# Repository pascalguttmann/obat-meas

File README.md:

# Obat - Measurement

KiCAD Project for the measurement electronics of Obat.

| TOP | BOT |
| ------------- | -------------- |
|  |  |
|  |  |

## License

This repository is licensed under the MIT license.

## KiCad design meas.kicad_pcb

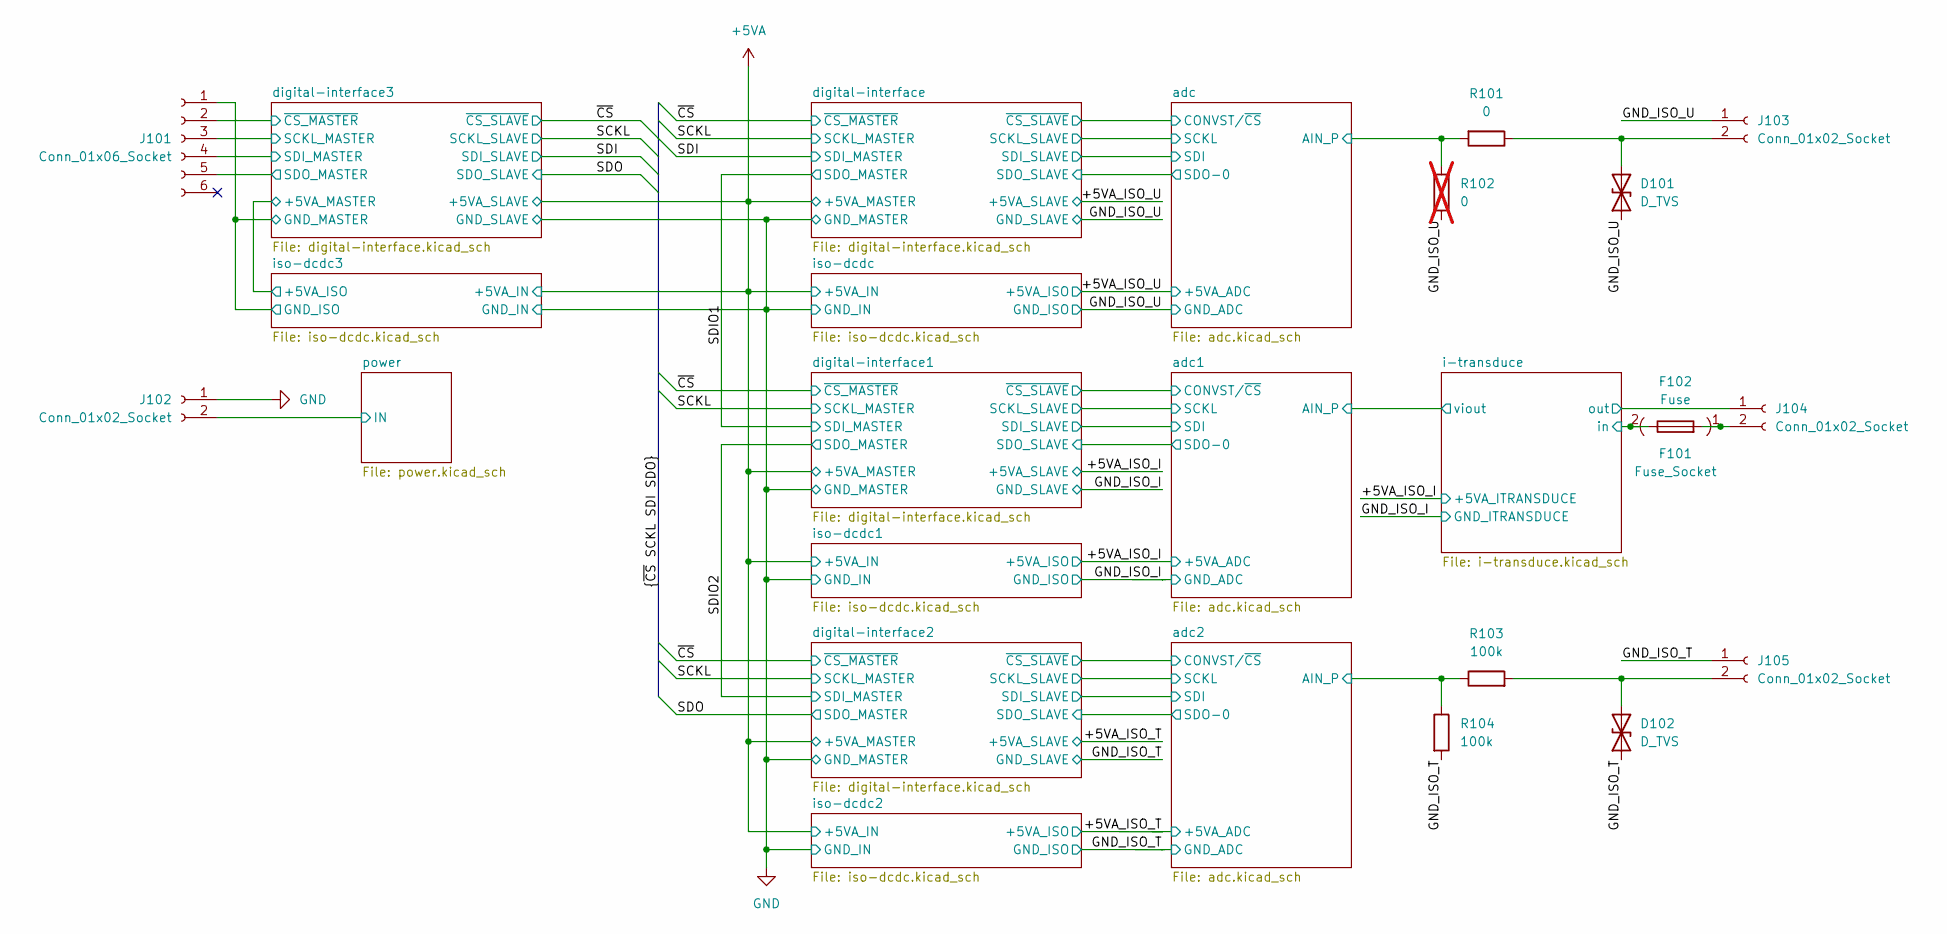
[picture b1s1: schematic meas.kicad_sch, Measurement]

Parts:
D101, D102: D_TVS; D_SOD-323_HandSoldering; MPN UDD32C24L01
F101: Fuse_Socket; FuseHolder_Blade_ATO_Littelfuse_FLR_178.6165; MPN 178.6165.0002
F102: Fuse; MPN 0287030.PXCN
J101: Conn_01x06_Socket; PhoenixContact_TDPT_2,5_6-SP-5,08_1x06_P5.08mm_Horizontal; MPN 1017507
J102, J103, J104, J105: Conn_01x02_Socket; PhoenixContact_TDPT_2,5_2-SP-5,08_1x02_P5.08mm_Horizontal; MPN 1017503
R101: 0; R_1210_3225Metric_Pad1.30x2.65mm_HandSolder; MPN RC1210JR-070RL
R102: 0; R_1210_3225Metric_Pad1.30x2.65mm_HandSolder; MPN RC1210JR-070RL; not fitted
R103, R104: 100k; R_1210_3225Metric_Pad1.30x2.65mm_HandSolder; MPN RC1210FR-07100KL

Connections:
/GND_ISO_T: D102.1 (A1), J105.1, R104.2; also elsewhere on the board
/GND_ISO_U: D101.1 (A1), J103.1, R102.1; also elsewhere on the board
/adc2/AIN_P: R103.1, R104.1; also elsewhere on the board
/adc/AIN_P: R101.2, R102.2; also elsewhere on the board
/digital-interface3/GND_MASTER: J101.1; also elsewhere on the board
/digital-interface3/SCKL_MASTER: J101.3; also elsewhere on the board
/digital-interface3/SDI_MASTER: J101.4; also elsewhere on the board
/digital-interface3/SDO_MASTER: J101.5; also elsewhere on the board
/digital-interface3/~CS_MASTER: J101.2; also elsewhere on the board
/i-transduce/in: F101.2, F102.1; also elsewhere on the board
/i-transduce/out: J104.1; also elsewhere on the board
/power/IN: J102.2; also elsewhere on the board
GND: J102.1; also elsewhere on the board
unnamed: D101.2 (A2), J103.2, R101.1
unnamed: D102.2 (A2), J105.2, R103.2
unnamed: F101.1, F102.2, J104.2

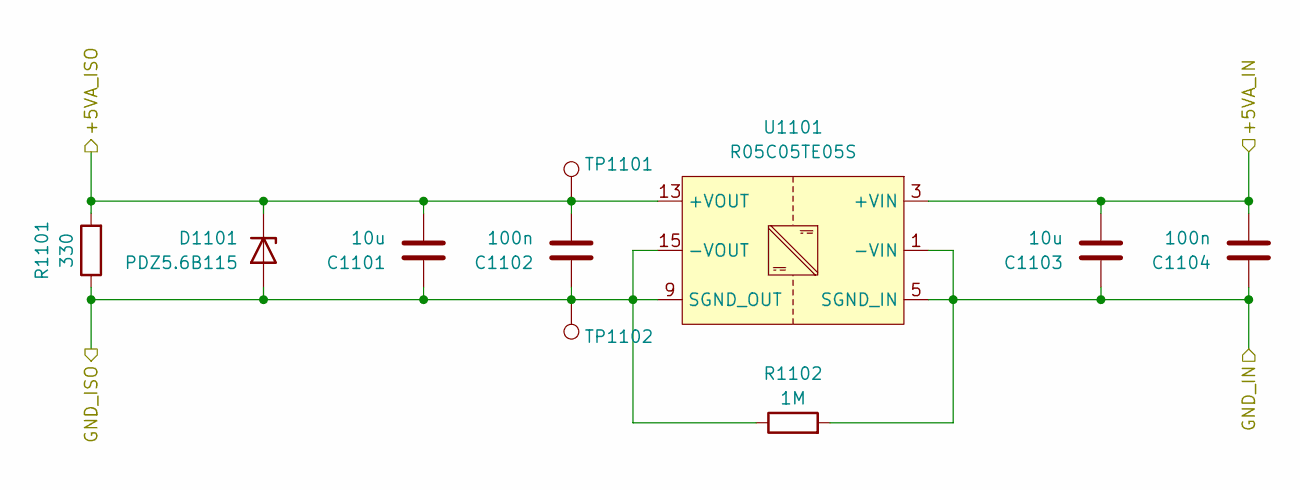
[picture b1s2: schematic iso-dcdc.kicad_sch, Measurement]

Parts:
C1101, C1103: 10u; C_1210_3225Metric_Pad1.33x2.70mm_HandSolder; MPN C1210C106K3RACTU
C1102, C1104: 100n; C_0805_2012Metric_Pad1.18x1.45mm_HandSolder; MPN C0805C104K3RACTU
D1101: PDZ5.6B115; D_SOD-323_HandSoldering; MPN PDZ5.6B,115
R1101: 330; R_1210_3225Metric_Pad1.30x2.65mm_HandSolder; MPN RC1210FR-07330RL
R1102: 1M; R_1210_3225Metric_Pad1.30x2.65mm_HandSolder; MPN RC1210FR-071ML
TP1101, TP1102: TP_0805_2012Metric; MPN RCTCTE
U1101: R05C05TE05S; SOIC-16W_7.5x10.3mm_P1.27mm; MPN R05C05TE05S-R

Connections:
/+5VA_ISO_U: C1101.2, C1102.2, D1101.1 (K), R1101.2, TP1101.1, U1101.13 (+VOUT), U1101.14 (+VOUT); also elsewhere on the board
/GND_ISO_U: C1101.1, C1102.1, D1101.2 (A), R1101.1, R1102.1, TP1102.1, U1101.9 (SGND_OUT), U1101.11 (SGND_OUT), U1101.12 (SGND_OUT), U1101.15 (-VOUT), U1101.16 (-VOUT); also elsewhere on the board
GND: C1103.1, C1104.1, R1102.2, U1101.1 (-VIN), U1101.2 (-VIN), U1101.5 (SGND_IN), U1101.6 (SGND_IN), U1101.7 (SGND_IN), U1101.8 (SGND_IN); also elsewhere on the board

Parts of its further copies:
C1201, C1203, C1301, C1303, C1401, C1403: 10u; C_1210_3225Metric_Pad1.33x2.70mm_HandSolder; MPN C1210C106K3RACTU
C1202, C1204, C1302, C1304, C1402, C1404: 100n; C_0805_2012Metric_Pad1.18x1.45mm_HandSolder; MPN C0805C104K3RACTU
D1201, D1301, D1401: PDZ5.6B115; D_SOD-323_HandSoldering; MPN PDZ5.6B,115
R1201, R1301, R1401: 330; R_1210_3225Metric_Pad1.30x2.65mm_HandSolder; MPN RC1210FR-07330RL
R1202, R1302, R1402: 1M; R_1210_3225Metric_Pad1.30x2.65mm_HandSolder; MPN RC1210FR-071ML
TP1201, TP1202, TP1301, TP1302, TP1401, TP1402: TP_0805_2012Metric; MPN RCTCTE
U1201, U1301, U1401: R05C05TE05S; SOIC-16W_7.5x10.3mm_P1.27mm; MPN R05C05TE05S-R

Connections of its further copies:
/+5VA_ISO_I: C1201.2, C1202.2, D1201.1 (K), R1201.2, TP1201.1, U1201.13 (+VOUT), U1201.14 (+VOUT); also elsewhere on the board
/+5VA_ISO_T: C1301.2, C1302.2, D1301.1 (K), R1301.2, TP1301.1, U1301.13 (+VOUT), U1301.14 (+VOUT); also elsewhere on the board
/GND_ISO_I: C1201.1, C1202.1, D1201.2 (A), R1201.1, R1202.1, TP1202.1, U1201.9 (SGND_OUT), U1201.11 (SGND_OUT), U1201.12 (SGND_OUT), U1201.15 (-VOUT), U1201.16 (-VOUT); also elsewhere on the board
/GND_ISO_T: C1301.1, C1302.1, D1301.2 (A), R1301.1, R1302.1, TP1302.1, U1301.9 (SGND_OUT), U1301.11 (SGND_OUT), U1301.12 (SGND_OUT), U1301.15 (-VOUT), U1301.16 (-VOUT); also elsewhere on the board
/digital-interface3/+5VA_MASTER: C1401.2, C1402.2, D1401.1 (K), R1401.2, TP1401.1, U1401.13 (+VOUT), U1401.14 (+VOUT); also elsewhere on the board
/digital-interface3/GND_MASTER: C1401.1, C1402.1, D1401.2 (A), R1401.1, R1402.1, TP1402.1, U1401.9 (SGND_OUT), U1401.11 (SGND_OUT), U1401.12 (SGND_OUT), U1401.15 (-VOUT), U1401.16 (-VOUT); also elsewhere on the board
GND: C1203.1, C1204.1, C1303.1, C1304.1, C1403.1, C1404.1, R1202.2, R1302.2, R1402.2, U1201.1 (-VIN), U1201.2 (-VIN), U1201.5 (SGND_IN), U1201.6 (SGND_IN), U1201.7 (SGND_IN), U1201.8 (SGND_IN), U1301.1 (-VIN), U1301.2 (-VIN), U1301.5 (SGND_IN), U1301.6 (SGND_IN), U1301.7 (SGND_IN), U1301.8 (SGND_IN), U1401.1 (-VIN), U1401.2 (-VIN), U1401.5 (SGND_IN), U1401.6 (SGND_IN), U1401.7 (SGND_IN), U1401.8 (SGND_IN); also elsewhere on the board

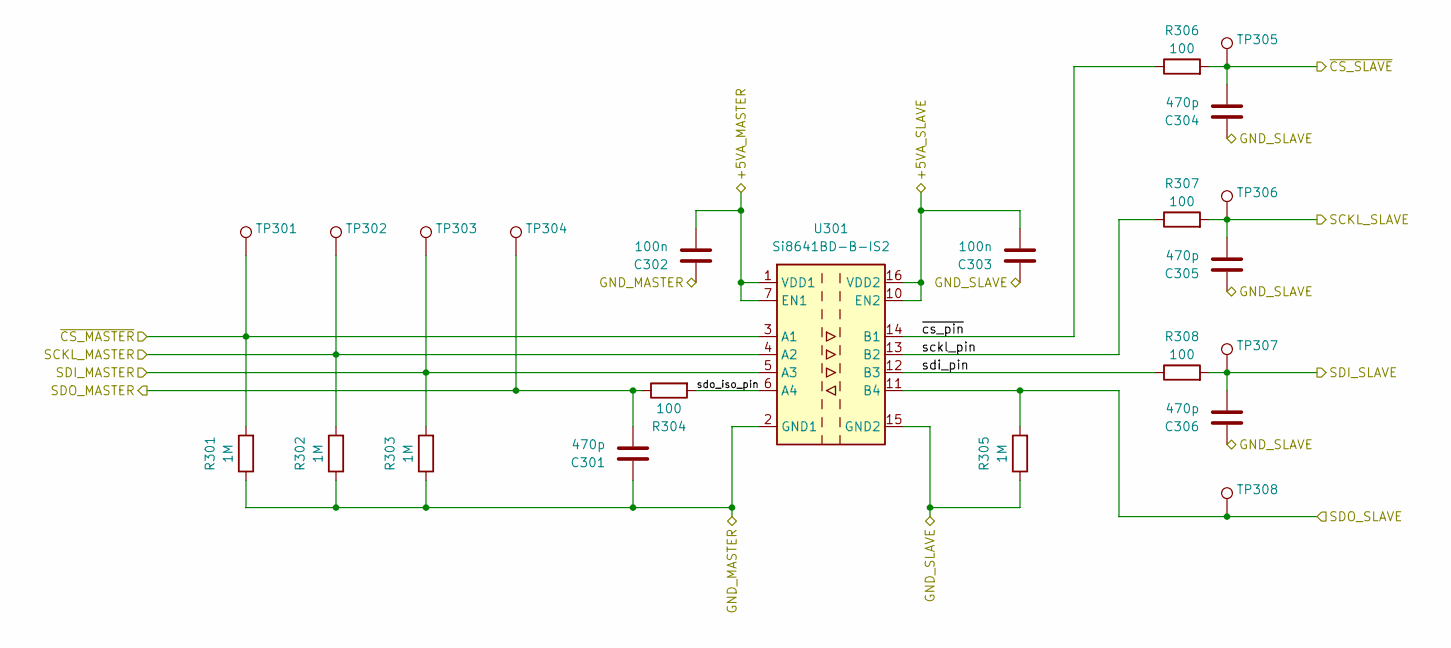
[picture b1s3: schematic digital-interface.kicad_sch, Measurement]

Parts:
C301, C304, C305, C306: 470p; C_0805_2012Metric_Pad1.18x1.45mm_HandSolder; MPN C0805C471K3RACTU
C302, C303: 100n; C_0805_2012Metric_Pad1.18x1.45mm_HandSolder; MPN C0805C104K3RACTU
R301, R302, R303, R305: 1M; R_1210_3225Metric_Pad1.30x2.65mm_HandSolder; MPN RC1210FR-071ML
R304, R306, R307, R308: 100; R_1210_3225Metric_Pad1.30x2.65mm_HandSolder; MPN RC1210FR-07100RL
TP301, TP302, TP303, TP304, TP305, TP306, TP307, TP308: TP_0805_2012Metric; MPN RCTCTE
U301: Si8641BD-B-IS2; SOIC-16W_7.5x10.3mm_P1.27mm; MPN SI8641BD-B-IS2

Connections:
/+5VA_ISO_I: C303.2, U301.10 (EN2), U301.16 (VDD2); also elsewhere on the board
/GND_ISO_I: C303.1, C304.1, C305.1, C306.1, R305.1, U301.9 (GND2), U301.15 (GND2); also elsewhere on the board
/SCKL: R302.2, TP302.1, U301.4 (A2); also elsewhere on the board
/SDIO1: R303.2, TP303.1, U301.5 (A3); also elsewhere on the board
/SDIO2: C301.2, R304.1, TP304.1; also elsewhere on the board
/adc1/CONVST/~CS: C304.2, R306.2, TP305.1; also elsewhere on the board
/adc1/SCKL: C305.2, R307.2, TP306.1; also elsewhere on the board
/adc1/SDI: C306.2, R308.2, TP307.1; also elsewhere on the board
/adc1/SDO-0: R305.2, TP308.1, U301.11 (B4); also elsewhere on the board
/digital-interface1/sckl_pin: R307.1, U301.13 (B2)
/digital-interface1/sdi_pin: R308.1, U301.12 (B3)
/digital-interface1/sdo_iso_pin: R304.2, U301.6 (A4)
/digital-interface1/~cs_pin: R306.1, U301.14 (B1)
/~CS: R301.2, TP301.1, U301.3 (A1); also elsewhere on the board
GND: C301.1, C302.1, R301.1, R302.1, R303.1, U301.2 (GND1), U301.8 (GND1); also elsewhere on the board

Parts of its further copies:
C201, C204, C205, C206, C401, C404, C405, C406, C501, C504, C505, C506: 470p; C_0805_2012Metric_Pad1.18x1.45mm_HandSolder; MPN C0805C471K3RACTU
C202, C203, C402, C403, C502, C503: 100n; C_0805_2012Metric_Pad1.18x1.45mm_HandSolder; MPN C0805C104K3RACTU
R201, R202, R203, R205, R401, R402, R403, R405, R501, R502, R503, R505: 1M; R_1210_3225Metric_Pad1.30x2.65mm_HandSolder; MPN RC1210FR-071ML
R204, R206, R207, R208, R404, R406, R407, R408, R504, R506, R507, R508: 100; R_1210_3225Metric_Pad1.30x2.65mm_HandSolder; MPN RC1210FR-07100RL
TP201, TP202, TP203, TP204, TP205, TP206, TP207, TP208, TP401, TP402, TP403, TP404, TP405, TP406, TP407, TP408, TP501, TP502, TP503, TP504, TP505, TP506, TP507, TP508: TP_0805_2012Metric; MPN RCTCTE
U201, U401, U501: Si8641BD-B-IS2; SOIC-16W_7.5x10.3mm_P1.27mm; MPN SI8641BD-B-IS2

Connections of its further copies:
/+5VA_ISO_T: C403.2, U401.10 (EN2), U401.16 (VDD2); also elsewhere on the board
/+5VA_ISO_U: C203.2, U201.10 (EN2), U201.16 (VDD2); also elsewhere on the board
/GND_ISO_T: C403.1, C404.1, C405.1, C406.1, R405.1, U401.9 (GND2), U401.15 (GND2); also elsewhere on the board
/GND_ISO_U: C203.1, C204.1, C205.1, C206.1, R205.1, U201.9 (GND2), U201.15 (GND2); also elsewhere on the board
/SCKL: C505.2, R202.2, R402.2, R507.2, TP202.1, TP402.1, TP506.1, U201.4 (A2), U401.4 (A2); also elsewhere on the board
/SDI: C506.2, R203.2, R508.2, TP203.1, TP507.1, U201.5 (A3)
/SDIO1: C201.2, R204.1, TP204.1; also elsewhere on the board
/SDIO2: R403.2, TP403.1, U401.5 (A3); also elsewhere on the board
/SDO: C401.2, R404.1, R505.2, TP404.1, TP508.1, U501.11 (B4)
/adc2/CONVST/~CS: C404.2, R406.2, TP405.1; also elsewhere on the board
/adc2/SCKL: C405.2, R407.2, TP406.1; also elsewhere on the board
/adc2/SDI: C406.2, R408.2, TP407.1; also elsewhere on the board
/adc2/SDO-0: R405.2, TP408.1, U401.11 (B4); also elsewhere on the board
/adc/CONVST/~CS: C204.2, R206.2, TP205.1; also elsewhere on the board
/adc/SCKL: C205.2, R207.2, TP206.1; also elsewhere on the board
/adc/SDI: C206.2, R208.2, TP207.1; also elsewhere on the board
/adc/SDO-0: R205.2, TP208.1, U201.11 (B4); also elsewhere on the board
/digital-interface2/sckl_pin: R407.1, U401.13 (B2)
/digital-interface2/sdi_pin: R408.1, U401.12 (B3)
/digital-interface2/sdo_iso_pin: R404.2, U401.6 (A4)
/digital-interface2/~cs_pin: R406.1, U401.14 (B1)
/digital-interface3/+5VA_MASTER: C502.2, U501.1 (VDD1), U501.7 (EN1); also elsewhere on the board
/digital-interface3/GND_MASTER: C501.1, C502.1, R501.1, R502.1, R503.1, U501.2 (GND1), U501.8 (GND1); also elsewhere on the board
/digital-interface3/SCKL_MASTER: R502.2, TP502.1, U501.4 (A2); also elsewhere on the board
/digital-interface3/SDI_MASTER: R503.2, TP503.1, U501.5 (A3); also elsewhere on the board
/digital-interface3/SDO_MASTER: C501.2, R504.1, TP504.1; also elsewhere on the board
/digital-interface3/sckl_pin: R507.1, U501.13 (B2)
/digital-interface3/sdi_pin: R508.1, U501.12 (B3)
/digital-interface3/sdo_iso_pin: R504.2, U501.6 (A4)
/digital-interface3/~CS_MASTER: R501.2, TP501.1, U501.3 (A1); also elsewhere on the board
/digital-interface3/~cs_pin: R506.1, U501.14 (B1)
/digital-interface/sckl_pin: R207.1, U201.13 (B2)
/digital-interface/sdi_pin: R208.1, U201.12 (B3)
/digital-interface/sdo_iso_pin: R204.2, U201.6 (A4)
/digital-interface/~cs_pin: R206.1, U201.14 (B1)
/~CS: C504.2, R201.2, R401.2, R506.2, TP201.1, TP401.1, TP505.1, U201.3 (A1), U401.3 (A1); also elsewhere on the board
GND: C201.1, C202.1, C401.1, C402.1, C503.1, C504.1, C505.1, C506.1, R201.1, R202.1, R203.1, R401.1, R402.1, R403.1, R505.1, U201.2 (GND1), U201.8 (GND1), U401.2 (GND1), U401.8 (GND1), U501.9 (GND2), U501.15 (GND2); also elsewhere on the board

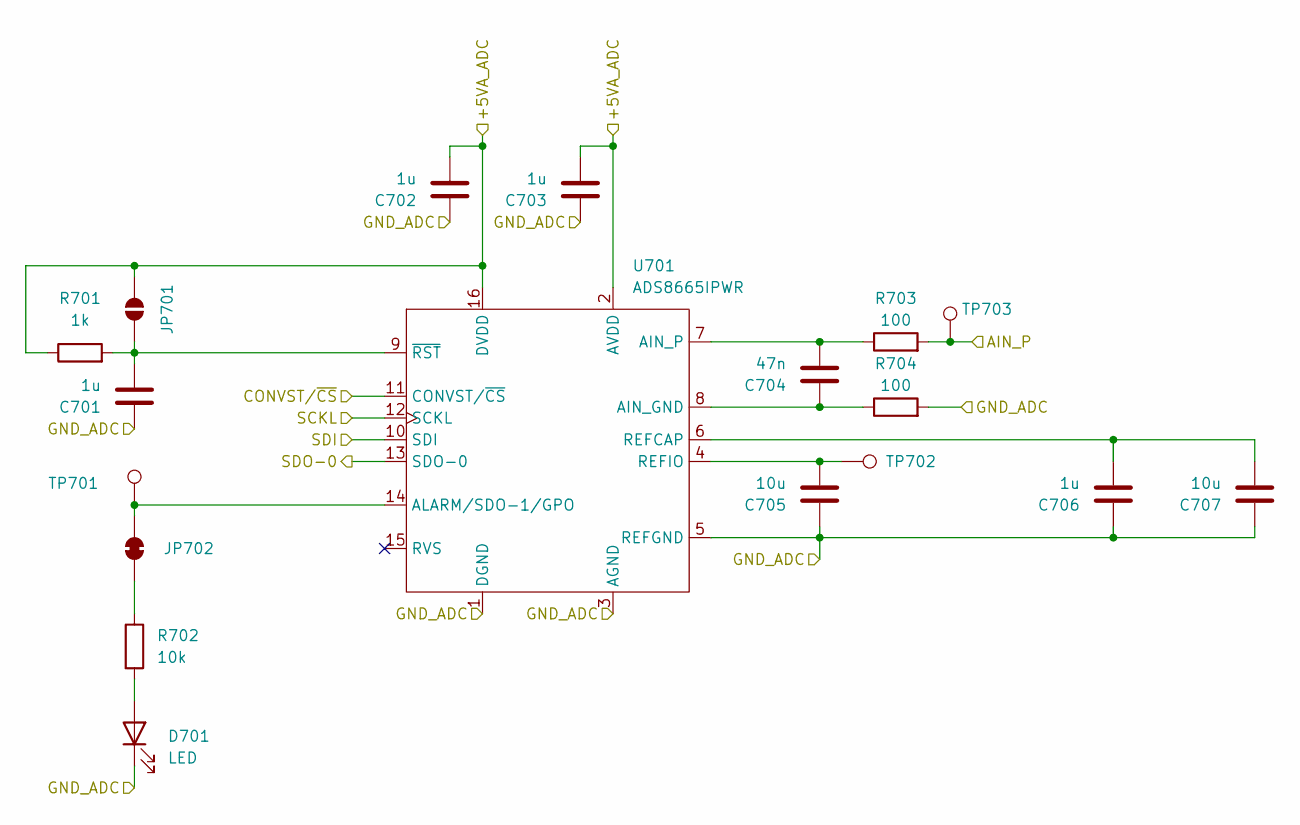
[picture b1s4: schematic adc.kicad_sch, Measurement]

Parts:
C701, C702, C703, C706: 1u; C_0603_1608Metric_Pad1.08x0.95mm_HandSolder; MPN C0603C105K4RACTU
C704: 47n; C_1206_3216Metric_Pad1.33x1.80mm_HandSolder; MPN C1206C473J5GACTU
C705, C707: 10u; C_1210_3225Metric_Pad1.33x2.70mm_HandSolder; MPN C1210C106K3RACTU
D701: LED; LED_0805_2012Metric_Pad1.15x1.40mm_HandSolder; MPN IN-S85CS5G
JP701: SolderJumper_2_Open; SolderJumper-2_P1.3mm_Open_RoundedPad1.0x1.5mm
JP702: SolderJumper_2_Bridged; SolderJumper-2_P1.3mm_Bridged-Soldermask-Paste_RoundedPad1.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
R701: 1k; R_1210_3225Metric_Pad1.30x2.65mm_HandSolder; MPN RC1210FR-071KL
R702: 10k; R_1210_3225Metric_Pad1.30x2.65mm_HandSolder; MPN RC1210FR-0710KL
R703, R704: 100; R_1210_3225Metric_Pad1.30x2.65mm_HandSolder; MPN RC1210FR-07100RL
TP701, TP702, TP703: TP_0805_2012Metric; MPN RCTCTE
U701: ADS8665IPWR; TSSOP-16_4.4x5mm_P0.65mm; MPN ADS8665IPWR

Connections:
/+5VA_ISO_I: C702.2, C703.2, JP701.1 (A), R701.1, U701.2 (AVDD), U701.16 (DVDD); also elsewhere on the board
/GND_ISO_I: C701.1, C702.1, C703.1, C705.1, C706.1, C707.1, D701.1 (K), R704.2, U701.1 (DGND), U701.3 (AGND), U701.5 (REFGND); also elsewhere on the board
/adc1/AIN_P: R703.2, TP703.1; also elsewhere on the board
/adc1/CONVST/~CS: U701.11 (CONVST/~CS); also elsewhere on the board
/adc1/SCKL: U701.12 (SCKL); also elsewhere on the board
/adc1/SDI: U701.10 (SDI); also elsewhere on the board
/adc1/SDO-0: U701.13 (SDO-0); also elsewhere on the board
unnamed: D701.2 (A), R702.2
unnamed: C701.2, JP701.2 (B), R701.2, U701.9 (~RST)
unnamed: JP702.1 (A), R702.1
unnamed: JP702.2 (B), TP701.1, U701.14 (ALARM/SDO-1/GPO)
unnamed: C704.1, R704.1, U701.8 (AIN_GND)
unnamed: C704.2, R703.1, U701.7 (AIN_P)
unnamed: C706.2, C707.2, U701.6 (REFCAP)
unnamed: C705.2, TP702.1, U701.4 (REFIO)

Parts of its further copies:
C601, C602, C603, C606, C801, C802, C803, C806: 1u; C_0603_1608Metric_Pad1.08x0.95mm_HandSolder; MPN C0603C105K4RACTU
C604, C804: 47n; C_1206_3216Metric_Pad1.33x1.80mm_HandSolder; MPN C1206C473J5GACTU
C605, C607, C805, C807: 10u; C_1210_3225Metric_Pad1.33x2.70mm_HandSolder; MPN C1210C106K3RACTU
D601, D801: LED; LED_0805_2012Metric_Pad1.15x1.40mm_HandSolder; MPN IN-S85CS5G
JP601, JP801: SolderJumper_2_Open; SolderJumper-2_P1.3mm_Open_RoundedPad1.0x1.5mm
JP602, JP802: SolderJumper_2_Bridged; SolderJumper-2_P1.3mm_Bridged-Soldermask-Paste_RoundedPad1.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
R601, R801: 1k; R_1210_3225Metric_Pad1.30x2.65mm_HandSolder; MPN RC1210FR-071KL
R602, R802: 10k; R_1210_3225Metric_Pad1.30x2.65mm_HandSolder; MPN RC1210FR-0710KL
R603, R604, R803, R804: 100; R_1210_3225Metric_Pad1.30x2.65mm_HandSolder; MPN RC1210FR-07100RL
TP601, TP602, TP603, TP801, TP802, TP803: TP_0805_2012Metric; MPN RCTCTE
U601, U801: ADS8665IPWR; TSSOP-16_4.4x5mm_P0.65mm; MPN ADS8665IPWR

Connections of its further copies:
/+5VA_ISO_T: C802.2, C803.2, JP801.1 (A), R801.1, U801.2 (AVDD), U801.16 (DVDD); also elsewhere on the board
/+5VA_ISO_U: C602.2, C603.2, JP601.1 (A), R601.1, U601.2 (AVDD), U601.16 (DVDD); also elsewhere on the board
/GND_ISO_T: C801.1, C802.1, C803.1, C805.1, C806.1, C807.1, D801.1 (K), R804.2, U801.1 (DGND), U801.3 (AGND), U801.5 (REFGND); also elsewhere on the board
/GND_ISO_U: C601.1, C602.1, C603.1, C605.1, C606.1, C607.1, D601.1 (K), R604.2, U601.1 (DGND), U601.3 (AGND), U601.5 (REFGND); also elsewhere on the board
/adc2/AIN_P: R803.2, TP803.1; also elsewhere on the board
/adc2/CONVST/~CS: U801.11 (CONVST/~CS); also elsewhere on the board
/adc2/SCKL: U801.12 (SCKL); also elsewhere on the board
/adc2/SDI: U801.10 (SDI); also elsewhere on the board
/adc2/SDO-0: U801.13 (SDO-0); also elsewhere on the board
/adc/AIN_P: R603.2, TP603.1; also elsewhere on the board
/adc/CONVST/~CS: U601.11 (CONVST/~CS); also elsewhere on the board
/adc/SCKL: U601.12 (SCKL); also elsewhere on the board
/adc/SDI: U601.10 (SDI); also elsewhere on the board
/adc/SDO-0: U601.13 (SDO-0); also elsewhere on the board
unnamed: D601.2 (A), R602.2
unnamed: D801.2 (A), R802.2
unnamed: C601.2, JP601.2 (B), R601.2, U601.9 (~RST)
unnamed: JP602.1 (A), R602.1
unnamed: JP602.2 (B), TP601.1, U601.14 (ALARM/SDO-1/GPO)
unnamed: C801.2, JP801.2 (B), R801.2, U801.9 (~RST)
unnamed: JP802.1 (A), R802.1
unnamed: JP802.2 (B), TP801.1, U801.14 (ALARM/SDO-1/GPO)
unnamed: C604.1, R604.1, U601.8 (AIN_GND)
unnamed: C604.2, R603.1, U601.7 (AIN_P)
unnamed: C606.2, C607.2, U601.6 (REFCAP)
unnamed: C605.2, TP602.1, U601.4 (REFIO)
unnamed: C804.1, R804.1, U801.8 (AIN_GND)
unnamed: C804.2, R803.1, U801.7 (AIN_P)
unnamed: C806.2, C807.2, U801.6 (REFCAP)
unnamed: C805.2, TP802.1, U801.4 (REFIO)

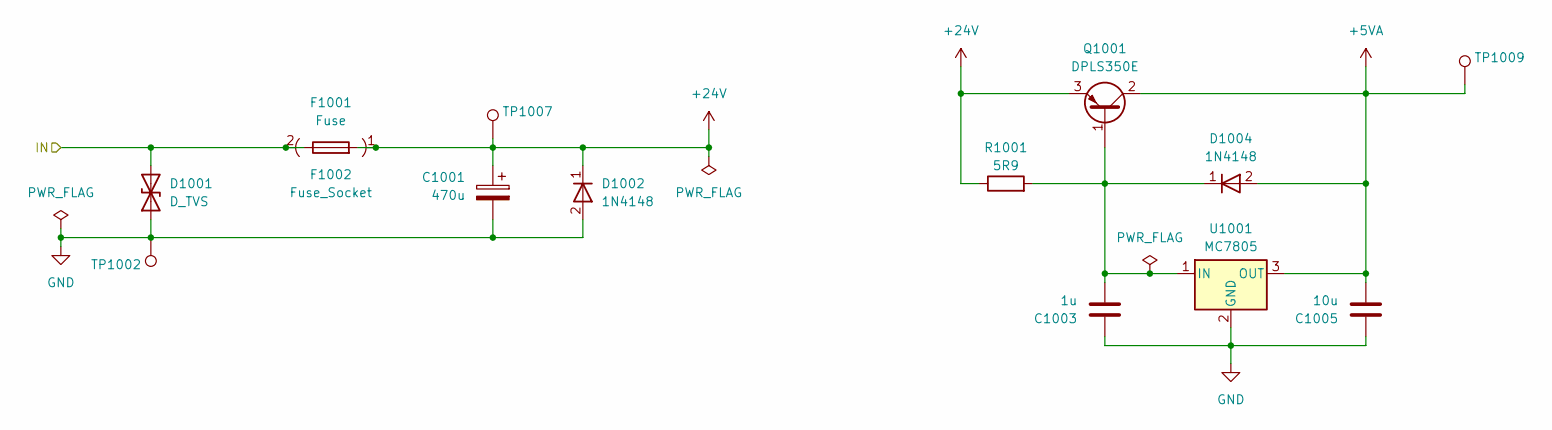
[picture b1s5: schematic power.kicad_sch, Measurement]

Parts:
C1001: 470u; CP_Elec_10x10; MPN EMZS350ARA471MHA0G
C1003: 1u; C_0603_1608Metric_Pad1.08x0.95mm_HandSolder; MPN C0603C105K4RACTU
C1005: 10u; C_1210_3225Metric_Pad1.33x2.70mm_HandSolder; MPN C1210C106K3RACTU
D1001: D_TVS; D_SOD-323_HandSoldering; MPN UDD32C24L01
D1002, D1004: 1N4148; D_SOD-123; MPN 1N4148W-7-F
F1001: Fuse; MPN 0287001.PXCN
F1002: Fuse_Socket; FuseHolder_Blade_ATO_Littelfuse_FLR_178.6165; MPN 178.6165.0002
Q1001: DPLS350E; SOT-223-3_TabPin2; MPN DPLS350E-13
R1001: 5R9; R_1210_3225Metric_Pad1.30x2.65mm_HandSolder; MPN RC1210FR-075R9L
TP1002, TP1007, TP1009: TP_0805_2012Metric; MPN RCTCTE
U1001: MC7805; TO-252-2; MPN MC7805BDTG

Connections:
+24V: C1001.1, D1002.1 (K), F1001.2, F1002.1, Q1001.3 (E), R1001.1; also elsewhere on the board
/power/IN: D1001.2 (A2), F1001.1, F1002.2; also elsewhere on the board
GND: C1001.2, C1003.1, D1001.1 (A1), D1002.2 (A), TP1002.1, U1001.2 (GND); also elsewhere on the board

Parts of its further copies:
C1002: 1u; C_0603_1608Metric_Pad1.08x0.95mm_HandSolder; MPN C0603C105K4RACTU
D1003: 1N4148; D_SOD-123; MPN 1N4148W-7-F
TP1003, TP1004: TP_0805_2012Metric; MPN RCTCTE

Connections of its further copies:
+24V: TP1003.1; also elsewhere on the board
GND: C1002.1; also elsewhere on the board

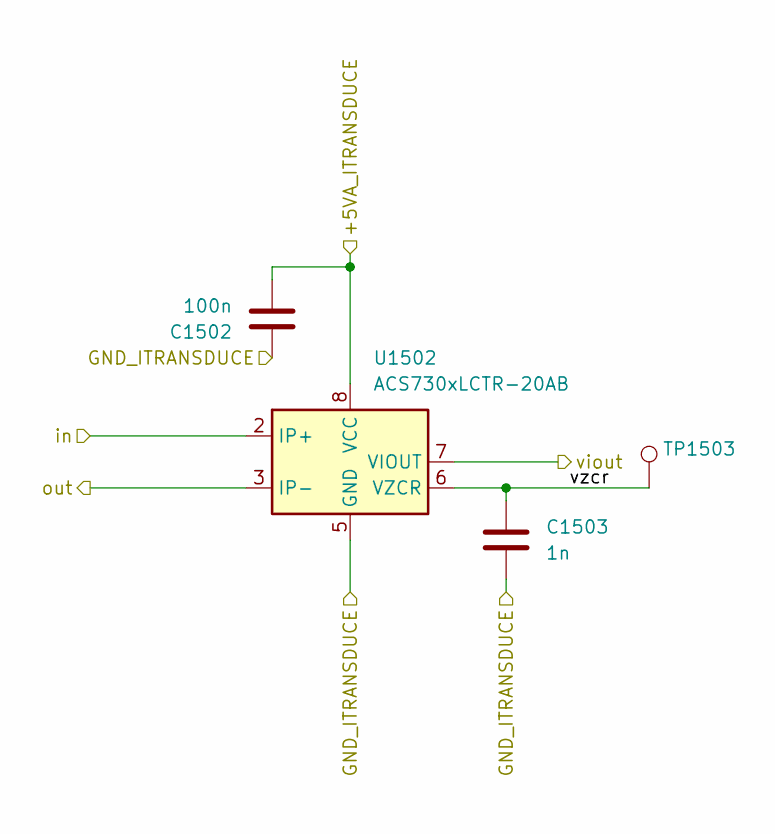
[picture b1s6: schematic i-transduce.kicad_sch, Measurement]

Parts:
C1502: 100n; C_0805_2012Metric_Pad1.18x1.45mm_HandSolder; MPN C0805C104K3RACTU
C1503: 1n; C_0805_2012Metric_Pad1.18x1.45mm_HandSolder; MPN C0805C102J5GACTU
TP1503: TP_0805_2012Metric; MPN RCTCTE
U1502: ACS730xLCTR-20AB; SOIC-8_3.9x4.9mm_P1.27mm; MPN ACS730KLCTR-20AB-T

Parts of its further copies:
C901: 100n; C_0805_2012Metric_Pad1.18x1.45mm_HandSolder; MPN C0805C104K3RACTU
C902: 1n; C_0805_2012Metric_Pad1.18x1.45mm_HandSolder; MPN C0805C102J5GACTU
TP902: TP_0805_2012Metric; MPN RCTCTE
U901: ACS730xLCTR-20AB; SOIC-8_3.9x4.9mm_P1.27mm; MPN ACS730KLCTR-20AB-T

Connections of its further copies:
/+5VA_ISO_I: C901.2, U901.8 (VCC); also elsewhere on the board
/GND_ISO_I: C901.1, C902.2, U901.5 (GND); also elsewhere on the board
/adc1/AIN_P: U901.7 (VIOUT); also elsewhere on the board
/i-transduce/in: U901.1 (IP+), U901.2 (IP+); also elsewhere on the board
/i-transduce/out: U901.3 (IP-), U901.4 (IP-); also elsewhere on the board
/i-transduce/vzcr: C902.1, TP902.1, U901.6 (VZCR)

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
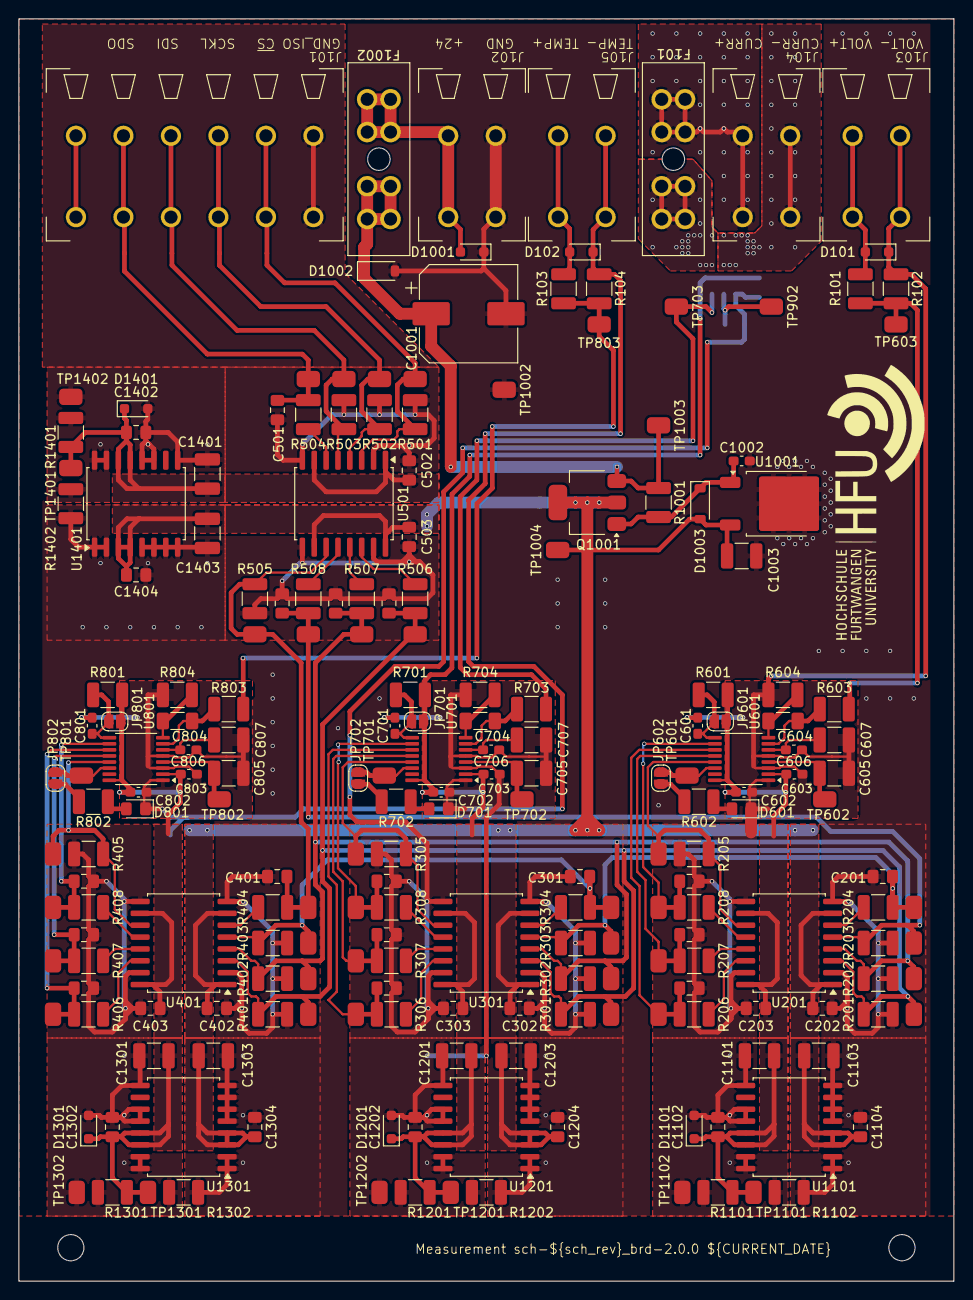
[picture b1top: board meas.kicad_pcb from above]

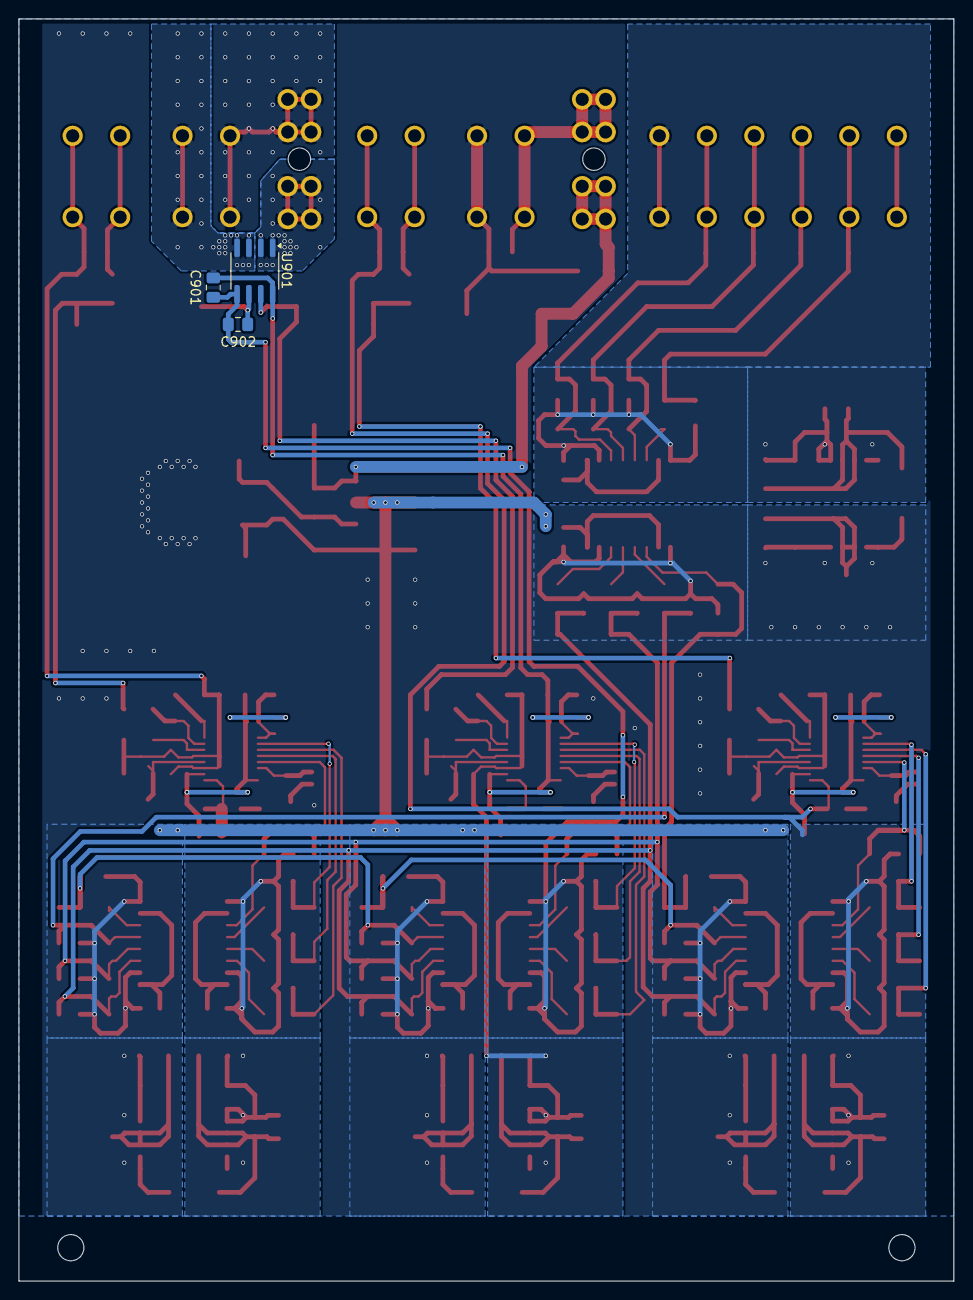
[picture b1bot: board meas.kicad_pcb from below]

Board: 2 copper layers, 100.0 x 135.0 mm, 215 parts (3 on the bottom side), 84 nets.

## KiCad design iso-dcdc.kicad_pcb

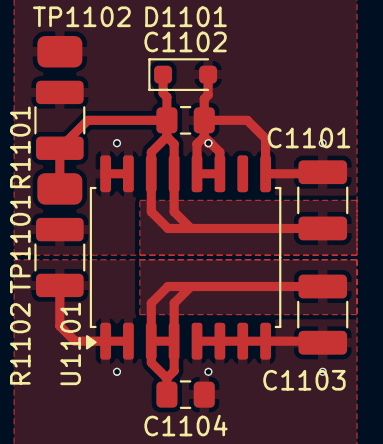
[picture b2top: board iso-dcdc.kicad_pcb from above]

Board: 2 copper layers, 10 parts (0 on the bottom side), 4 nets.

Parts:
C1101, C1103: 10u; C_1210_3225Metric_Pad1.33x2.70mm_HandSolder
C1102, C1104: 100n; C_0805_2012Metric_Pad1.18x1.45mm_HandSolder
D1101: PDZ5.6B115; D_SOD-323_HandSoldering
R1101: 330; R_1210_3225Metric_Pad1.30x2.65mm_HandSolder
R1102: 1M; R_1210_3225Metric_Pad1.30x2.65mm_HandSolder
TP1101, TP1102: TP_0805_2012Metric
U1101: R05C05TE05S; SOIC-16W_7.5x10.3mm_P1.27mm

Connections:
/+5VA_IN: C1103.2, C1104.2, U1101.3 (+VIN), U1101.4 (+VIN)
/+5VA_ISO: C1101.2, C1102.2, D1101.1 (K), R1101.2, TP1101.1, U1101.13 (+VOUT), U1101.14 (+VOUT)
/GND_IN: C1103.1, C1104.1, R1102.2, U1101.1 (-VIN), U1101.2 (-VIN), U1101.5 (SGND_IN), U1101.6 (SGND_IN), U1101.7 (SGND_IN), U1101.8 (SGND_IN)
/GND_ISO: C1101.1, C1102.1, D1101.2 (A), R1101.1, R1102.1, TP1102.1, U1101.9 (SGND_OUT), U1101.11 (SGND_OUT), U1101.12 (SGND_OUT), U1101.15 (-VOUT), U1101.16 (-VOUT)

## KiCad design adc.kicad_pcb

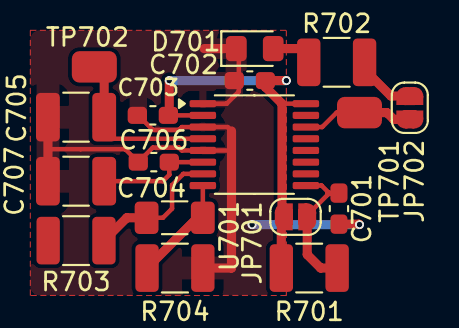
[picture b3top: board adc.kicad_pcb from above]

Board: 2 copper layers, 17 parts (0 on the bottom side), 2 nets.

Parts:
C701, C702, C703, C706: 1u; C_0603_1608Metric_Pad1.08x0.95mm_HandSolder
C704: 47n; C_1206_3216Metric_Pad1.33x1.80mm_HandSolder
C705, C707: 10u; C_1210_3225Metric_Pad1.33x2.70mm_HandSolder
D701: LED; LED_0805_2012Metric_Pad1.15x1.40mm_HandSolder
JP701: SolderJumper_2_Open; SolderJumper-2_P1.3mm_Open_RoundedPad1.0x1.5mm
JP702: SolderJumper_2_Bridged; SolderJumper-2_P1.3mm_Bridged-Soldermask-Paste_RoundedPad1.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
R701: 1k; R_1210_3225Metric_Pad1.30x2.65mm_HandSolder
R702: 10k; R_1210_3225Metric_Pad1.30x2.65mm_HandSolder
R703, R704: 100; R_1210_3225Metric_Pad1.30x2.65mm_HandSolder
TP701, TP702: TP_0805_2012Metric
U701: ADS8665IPWR; TSSOP-16_4.4x5mm_P0.65mm

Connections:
/+5VA_ADC: C702.2, C703.2, JP701.1 (A), R701.1, U701.2 (AVDD), U701.16 (DVDD)
/GND_ADC: C701.1, C702.1, C703.1, C705.1, C706.1, C707.1, D701.1 (K), R704.2, U701.1 (DGND), U701.3 (AGND), U701.5 (REFGND)

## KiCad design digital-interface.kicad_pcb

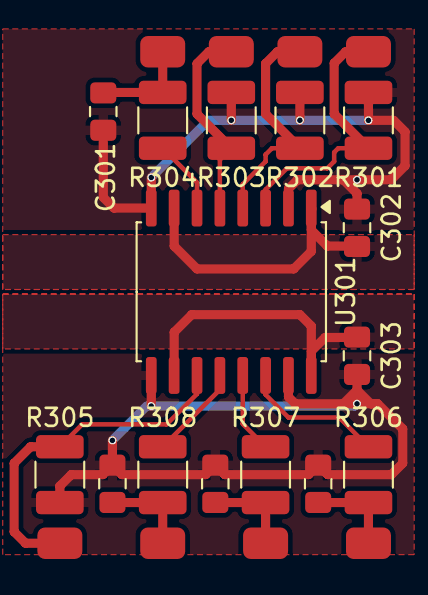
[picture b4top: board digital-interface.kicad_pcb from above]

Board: 2 copper layers, 23 parts (0 on the bottom side), 16 nets.

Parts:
C301, C304, C305, C306: 470p; C_0805_2012Metric_Pad1.18x1.45mm_HandSolder
C302, C303: 100n; C_0805_2012Metric_Pad1.18x1.45mm_HandSolder
R301, R302, R303, R305: 1M; R_1210_3225Metric_Pad1.30x2.65mm_HandSolder
R304, R306, R307, R308: 100; R_1210_3225Metric_Pad1.30x2.65mm_HandSolder
TP301, TP302, TP303, TP304, TP305, TP306, TP307, TP308: TP_0805_2012Metric
U301: Si8641BD-B-IS2; SOIC-16W_7.5x10.3mm_P1.27mm

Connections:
/+5VA_MASTER: C302.2, U301.1 (VDD1), U301.7 (EN1)
/+5VA_SLAVE: C303.2, U301.10 (EN2), U301.16 (VDD2)
/GND_MASTER: C301.1, C302.1, R301.1, R302.1, R303.1, U301.2 (GND1), U301.8 (GND1)
/GND_SLAVE: C303.1, C304.1, C305.1, C306.1, R305.1, U301.9 (GND2), U301.15 (GND2)
/SCKL_MASTER: R302.2, TP302.1, U301.4 (A2)
/SCKL_SLAVE: C305.2, R307.2, TP306.1
/SDI_MASTER: R303.2, TP303.1, U301.5 (A3)
/SDI_SLAVE: C306.2, R308.2, TP307.1
/SDO_MASTER: C301.2, R304.1, TP304.1
/SDO_SLAVE: R305.2, TP308.1, U301.11 (B4)
/sckl_pin: R307.1, U301.13 (B2)
/sdi_pin: R308.1, U301.12 (B3)
/sdo_iso_pin: R304.2, U301.6 (A4)
/~CS_MASTER: R301.2, TP301.1, U301.3 (A1)
/~CS_SLAVE: C304.2, R306.2, TP305.1
/~cs_pin: R306.1, U301.14 (B1)

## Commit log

2025-02-22 add .gitignore for KiCad Project
2025-02-22 add MIT license
2025-02-22 add README
2025-02-22 add 3d_models for pcb rendering
2025-02-22 add kicad project and schematic
2025-02-22 add digital-interface schematic
2025-02-22 add adc schematic
2025-02-22 add i-transduce schematic
2025-02-22 fix annotation for imported schematics (page prefix)
2025-02-22 add power schematic
2025-02-22 add overview schematic wiring
2025-02-22 fix digital-interface schematic connections
2025-02-22 add export of symbol libray, edit symbol links
2025-02-22 add meas.kicad_pcb from template with board outline
2025-02-22 add export of footprint library, edit footprint links
2025-02-22 add datasheets
2025-02-22 add connector placement
2025-02-22 add coarse placement of sub circuits
2025-02-22 add adc sub-layout
2025-02-23 separate digital-interface and iso-dcdc
2025-02-23 add interconnect layout
2025-02-23 fix filled zone netnumbers
2025-02-23 resize pcb to 100x130 mm^2
2025-02-23 edit silkscreen
2025-02-23 add plotted exports
2025-02-23 add 3d model images
2025-03-06 fix wrong fuse in bom
2025-03-06 fix netlist error in schematic and layout
    GND planes of isodcdc and adc of current measurement were not connected and now are connected.
2025-03-08 change resitor divider for temperature input for higher accuracy
